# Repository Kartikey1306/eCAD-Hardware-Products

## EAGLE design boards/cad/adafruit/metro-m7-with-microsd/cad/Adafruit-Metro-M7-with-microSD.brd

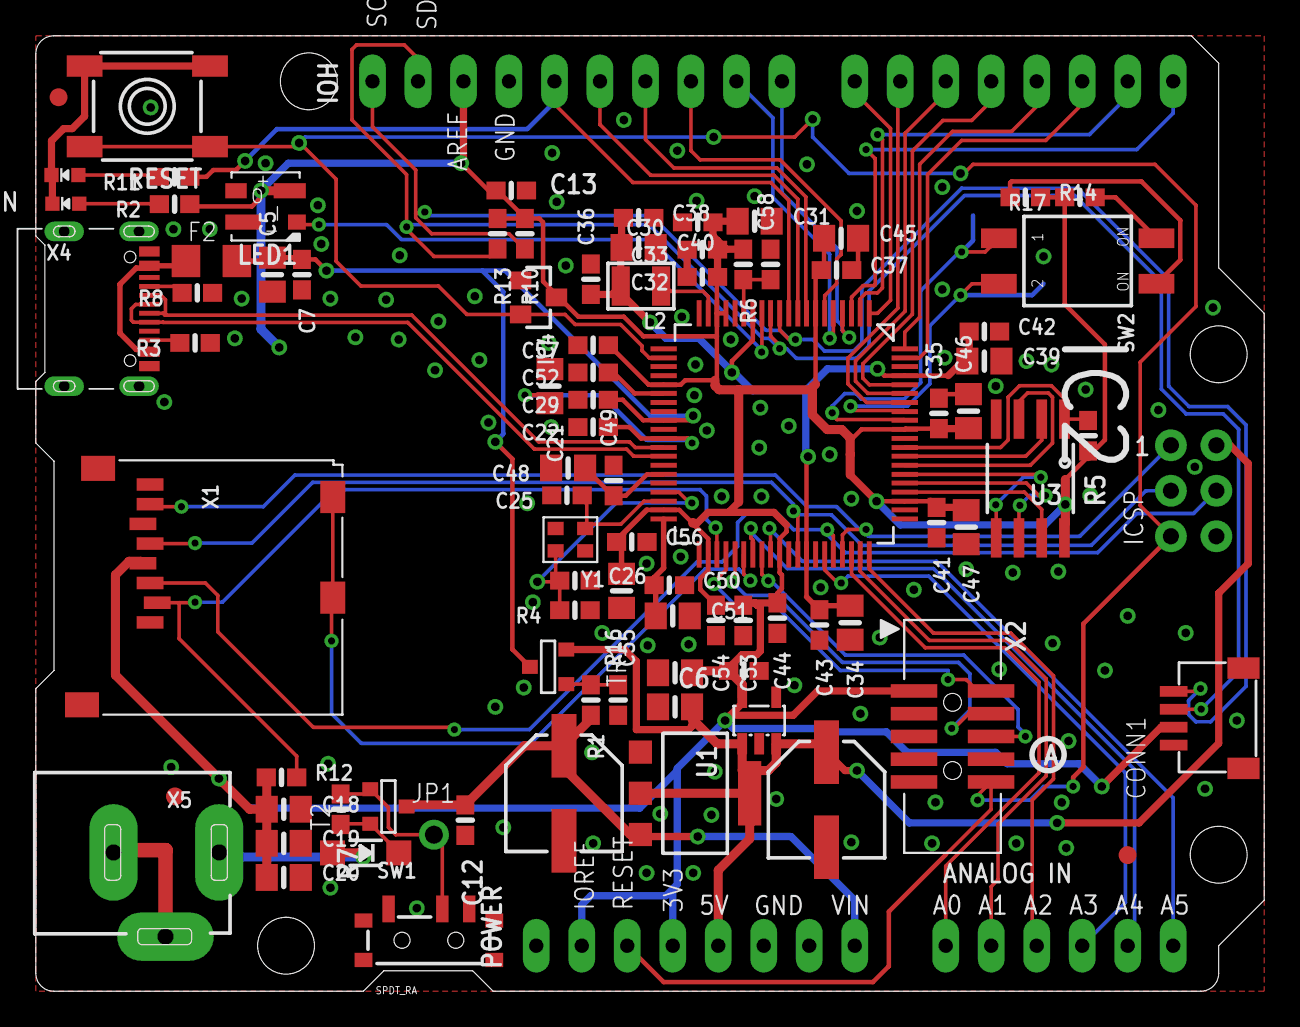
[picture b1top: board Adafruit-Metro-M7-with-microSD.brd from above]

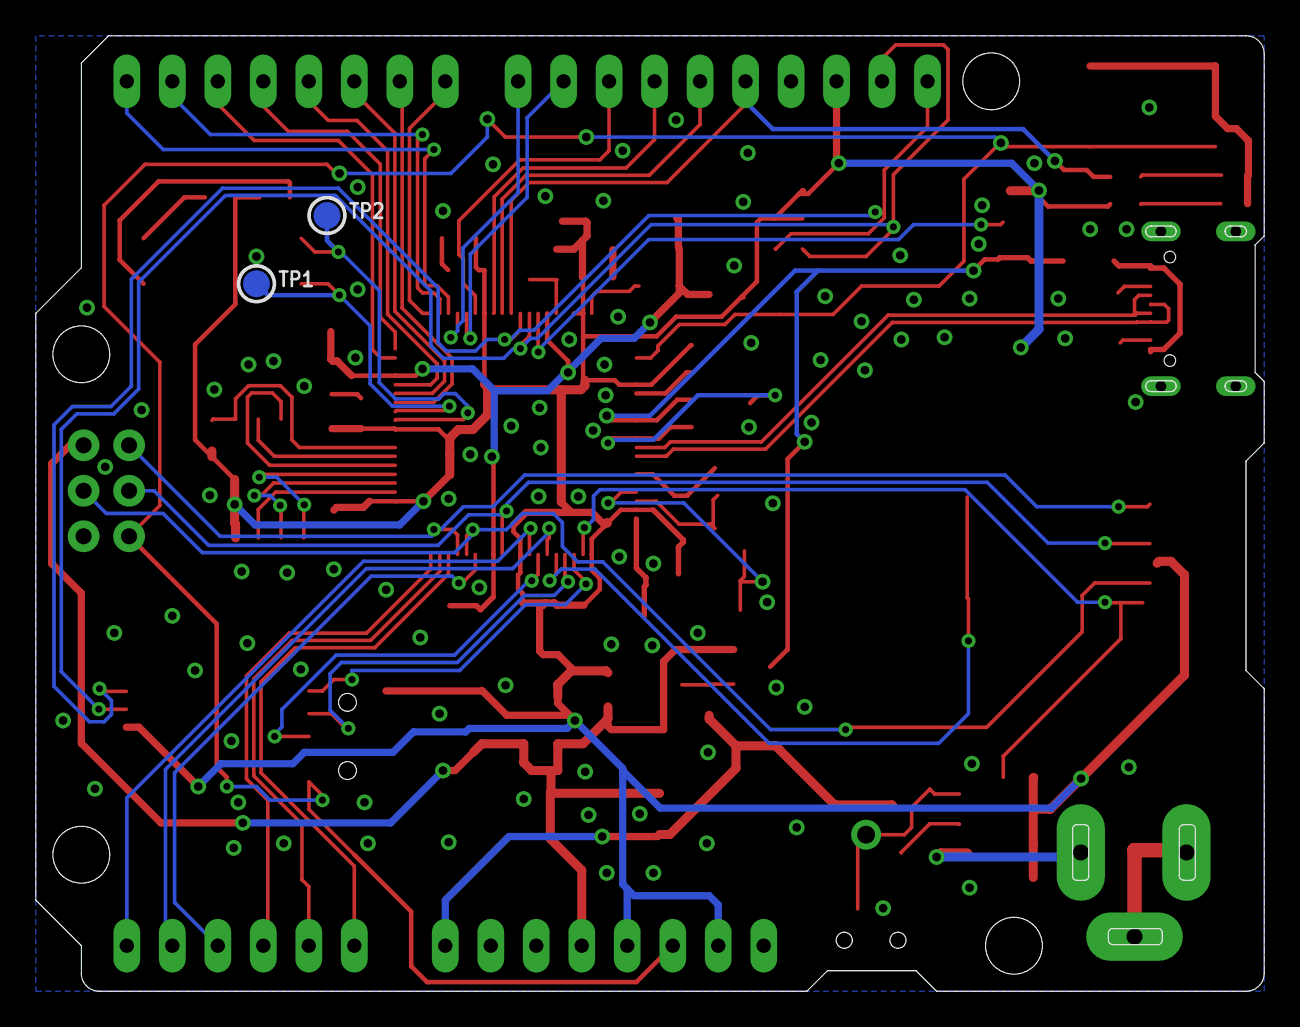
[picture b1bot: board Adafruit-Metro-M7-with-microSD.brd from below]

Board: 2 copper layers, 68.6 x 53.3 mm, 97 parts (3 on the bottom side), 67 nets.

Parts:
AD: 1x6F; 1X06_OVALWAVE
C2, C3, C5, C18, C19, C20, C21, C31, C39, C40, C45, C46, C47, C48, C51, C55: 10uF; 0805-NO
C6, C7, C12, C13, C22, C32, C35, C37, C41, C43: 0.1uF; 0603-NO
C25, C26: 16pF; 0603-NO
C29, C30, C36, C42, C44, C54: 1uF; 0603-NO
C33, C38, C49, C50, C52, C53, C56, C57, C58: 0.22uF; 0603-NO
C34: 22uF; 0805-NO
CONN1: STEMMA_I2C_QT; JST_SH4
D1: MBR120; SOD-123
F2: FUSE; R1206
FD1, FD2, FD3: FIDUCIAL_1MM
IC2: IMX_RT1010; QFP50P1400X1400X160-80N
IC4: APX80X_SA; SOT23-WIDE
ICSP: 2x3M; 2X03_ROUND_70MIL
IOH: 1x10F; 1X10_OVALWAVE
IOL: 1x8F; 1X08_OVALWAVE
JP1: 1X01_ROUND
L: RED; CHIPLED_0603_NOOUTLINE
L2: 4.7uH; INDUCTOR_1007
LED1: WS2812B_3535FULL; LED3535_FULLPADS
ON: GREEN; CHIPLED_0603_NOOUTLINE
PC1, PC2: 47uF/25V; PANASONIC_D
POWER: 1x8F; 1X08_OVALWAVE
R1, R16: 100K; 0603-NO
R2, R3, R8, R11, R14, R17: 5.1K; 0603-NO
R4: 2.2M; 0603-NO
R5, R7, R10, R12, R13: 10K; 0603-NO
R6: 30K; 0603-NO
RESET: 6x6mm; 6MMX6MM_TACTILE_SMT
SW1: SPDT_RA; SPDT_SMT_SSSS811101
SW2: DIP2; DIPSWITCH_2PIN
T2: DMP3098L-7; SOT-23
TP1, TP2: TESTPOINT_ROUND_1.5MM
TR1: DMP3098L-7; SOT-23
U1: NCP1117ST50T3G; SOT223-R
U2: AP2112K-3.3; SOT23-DBV
U3: W25Q64JV; SOIC8_208MIL
U$11: PCBFEAT-REV-040
U$12: M7_RT1011SD_TOP
U$19: M7_RT1011SD_BOT
X1: MICROSD
X2: 2x5 0.05" SWD; 2X05_1.27MM_BOX_POSTS
X4: USB C; USB_C_CUSB31-CFM2AX-01-X
X5: 2.1mm; DCJACK_2MM_PTH
Y1: 24MHz 10pF; CRYSTAL_2.5X2

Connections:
3.3V: C3.2, C6.2, C13.1, C18.1, C19.1, C20.1, C30.1, C31.1, C32.1, C33.1, C35.1, C37.1, C41.1, C44.1, C45.1, C46.1, C47.1, C53.1, C54.1, C55.1, C56.1, C57.1, CONN1.2, IC2.7, IC2.17, IC2.18, IC2.25, IC2.39, IC2.42, IC2.50, IC2.63, IC2.71, IC4.3, IOH.3, LED1.2, POWER.2, POWER.4, R2.1, R5.2, R6.1, R10.1, R12.1, R13.1, R14.2, R17.2, U2.5, U3.8, X1.4, X2.1
!RESET: IC2.22, IC4.2, ICSP.5, POWER.3, RESET.B, RESET.B', X2.10
+5V: C2.2, ICSP.2, PC2.+, POWER.5, TR1.2, U1.2, U1.4, U2.1, U2.3
A0: AD.1, IC2.58
A1: AD.2, IC2.59
A2: AD.3, IC2.60
A3: AD.4, IC2.55
A4: AD.5, IC2.47
A5: AD.6, IC2.49
BOOT_MODE0: IC2.72, SW2.1OFF, TP2.P$1
BOOT_MODE1: IC2.73, SW2.2OFF, TP1.P$1
D2: IC2.79, IOL.6
D3: IC2.80, IOL.5
D4: IC2.76, IOL.4
D5: IC2.75, IOL.3
D6: IC2.74, IOL.2
D7: IC2.1, IOL.1
D8: IC2.4, IOH.10
D9: IC2.5, IOH.9
D10: IC2.6, IOH.8
D11: IC2.8, IOH.7
D12: IC2.9, IOH.6
D13: IC2.10, IOH.5, R11.1
D+: IC2.33, X4.A6, X4.B6
D-: IC2.32, X4.A7, X4.B7
DCDC: IC2.19, L2.P$1
FLASH_CS: IC2.69, R5.1, U3.1
FLASH_IO0: IC2.66, U3.5
FLASH_IO1: IC2.68, U3.2
FLASH_IO2: IC2.67, U3.3
FLASH_IO3: IC2.64, U3.7
FLASH_SCK: IC2.65, U3.6
GND: C2.1, C3.1, C5.1, C6.1, C7.2, C12.2, C13.2, C18.2, C19.2, C20.2, C21.1, C22.2, C25.2, C26.2, C29.2, C30.2, C31.2, C32.2, C33.2, C34.2, C35.2, C36.2, C37.2, C38.2, C39.2, C40.2, C41.2, C42.2, C43.2, C44.2, C45.2, C46.2, C47.2, C48.2, C49.2, C50.2, C51.2, C52.2, C53.2, C54.2, C55.2, C56.2, C57.2, C58.2, CONN1.1, CONN1.MT1, CONN1.MT2, IC2.16, IC2.20, IC2.23, IC2.27, IC2.30, IC2.34, IC2.41, IC2.54, IC2.61, IC2.78, IC4.1, ICSP.6, IOH.4, L.C, LED1.4, ON.C, PC1.-, PC2.-, POWER.6, POWER.7, R3.1, R4.1, R8.1, R16.1, RESET.A, RESET.A', SW1.A, U1.1, U2.2, U3.4, X1.6, X1.MT1, X1.MT2, X2.3, X2.5, X4.A1B12, X4.B1A12, X5.GND, X5.GNDBREAK
MISO: IC2.57, ICSP.1, X1.7
MOSI: IC2.56, ICSP.4, X1.3
unnamed: L.A, R11.2
unnamed: ON.A, R2.2
unnamed: R14.1, SW2.2ON
unnamed: R17.1, SW2.1ON
unnamed: R8.2, X4.A5
unnamed: R3.2, X4.B5
unnamed: C26.1, IC2.37, R4.2, Y1.3
unnamed: C25.1, IC2.38, Y1.1
unnamed: R1.1, R16.2, TR1.3
unnamed: D1.C, R7.2, T2.2
NEOPIX: IC2.13, LED1.1
PSW: C58.1, IC2.15, R6.2
PWRIN: D1.A, X5.PWR
PWR_SWITCH: JP1.1, R7.1, SW1.B, T2.3
RXD: IC2.3, IOL.8
SCK: IC2.52, ICSP.3, X1.5
SCL: CONN1.4, IC2.11, IOH.1, R10.2
SDA: CONN1.3, IC2.12, IOH.2, R13.2
SD_CD: IC2.46, X1.CD1, X1.CD2
SD_CS: IC2.43, R12.2, X1.2
SVCS_CAP: C52.1, IC2.26
SWCLK: IC2.45, X2.4
SWDIO: IC2.44, X2.2
SWO: IC2.48, X2.6
TXD: IC2.2, IOL.7
USB_CAP: C21.2, C22.1, IC2.31
VBUS: C5.2, C7.1, C29.1, F2.2, IC2.29, TR1.1
VBUS_UNFUSE: F2.1, X4.A4B9, X4.B4A9
VDDA_1P1_CAP: C50.1, C51.1, IC2.40
VDDA_2P5_CAP: C48.1, C49.1, IC2.35
VDD_SOC_IN: C34.1, C36.1, C38.1, C39.1, C40.1, C42.1, C43.1, IC2.14, IC2.53, IC2.77, L2.P$2
VIN: C12.1, PC1.+, POWER.8, R1.2, T2.1, U1.3

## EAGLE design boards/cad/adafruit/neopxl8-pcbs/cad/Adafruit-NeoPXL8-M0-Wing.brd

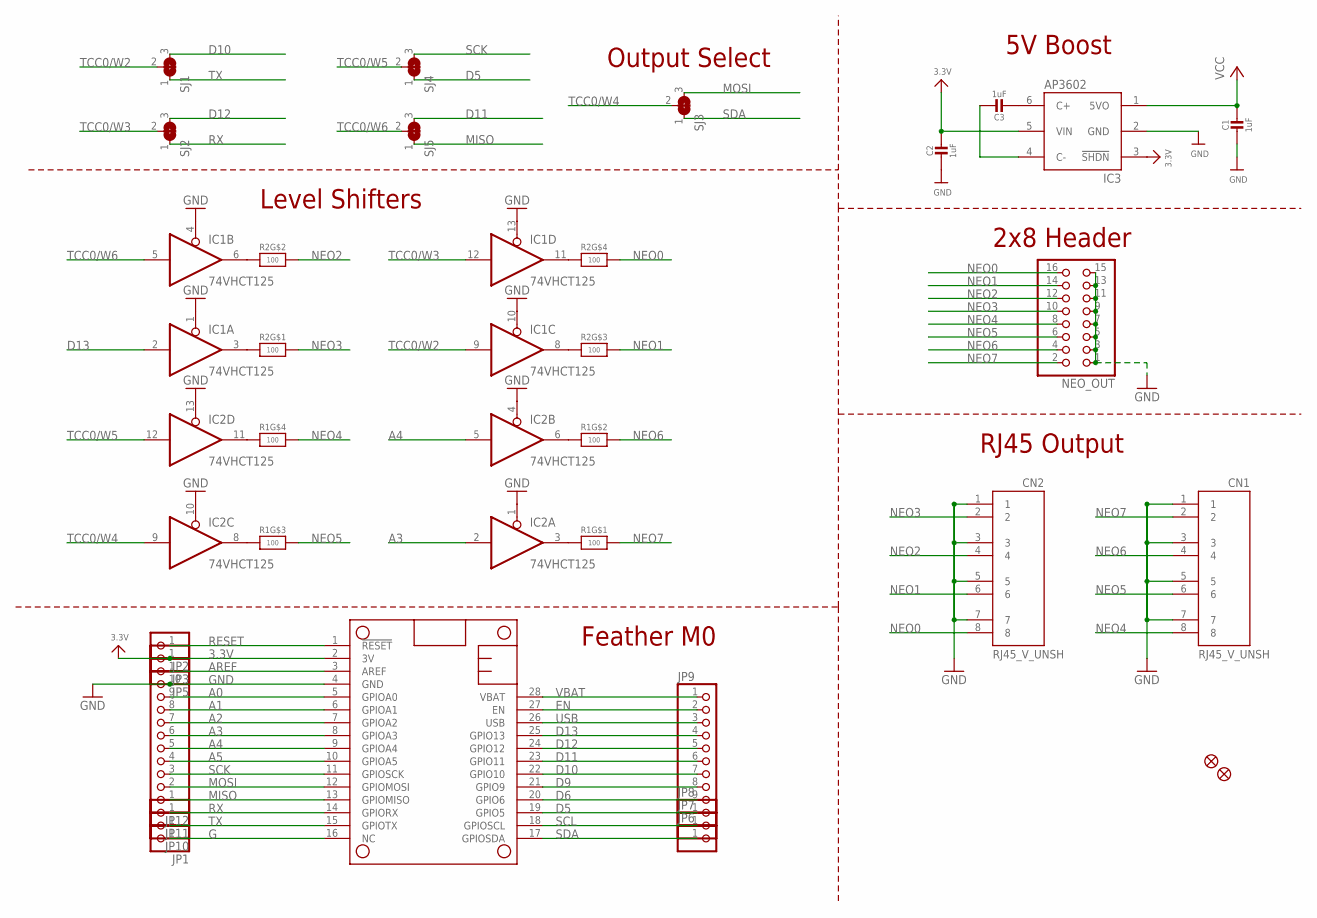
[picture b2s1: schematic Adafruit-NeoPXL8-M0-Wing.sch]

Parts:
C1, C2, C3: 1uF; 0603-NO
CN1, CN2: RJ45_V_UNSH; RJ45_VERTICAL_UNSHIELDED
FID1, FID2: FIDUCIAL_1MM
IC1, IC2: 74VHCT125; TSSOP14
IC3: AP3602; SOT23-6
JP1, JP2, JP3, JP5, JP6, JP7, JP8, JP10, JP11: HEADER-1X1ROUND; 1X01_ROUND
JP9: HEADER-1X970MIL; 1X09_ROUND_70
JP12: HEADER-1X10ROUND; 1X10_ROUND
MS1: FEATHERWING
NEO_OUT: HEADER-2X8; 2X08
R1, R2: 100; RESPACK_4X0603
SJ1, SJ2, SJ3, SJ4, SJ5: SOLDERJUMPER_2WAY; SOLDERJUMPER_2WAY_OPEN_NOPASTE

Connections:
3.3V: C2.1, IC3.3 (!SHDN), IC3.5 (VIN), JP3.1, MS1.2 (3V)
A0: JP12.9, MS1.5 (GPIOA0)
A1: JP12.8, MS1.6 (GPIOA1)
A2: JP12.7, MS1.7 (GPIOA2)
A3: IC2.2 (I), JP12.6, MS1.8 (GPIOA3)
A4: IC2.5 (I), JP12.5, MS1.9 (GPIOA4)
A5: JP12.4, MS1.10 (GPIOA5)
AREF: JP5.1, MS1.3 (AREF)
D5: JP8.1, MS1.19 (GPIO5), SJ4.1
D6: JP9.9, MS1.20 (GPIO6)
D9: JP9.8, MS1.21 (GPIO9)
D10: JP9.7, MS1.22 (GPIO10), SJ1.3
D11: JP9.6, MS1.23 (GPIO11), SJ5.3
D12: JP9.5, MS1.24 (GPIO12), SJ2.3
D13: IC1.2 (I), JP9.4, MS1.25 (GPIO13)
EN: JP9.2, MS1.27 (EN)
G: JP1.1, MS1.16 (NC)
GND: C1.2, C2.2, CN1.1, CN1.3, CN1.5, CN1.7, CN2.1, CN2.3, CN2.5, CN2.7, IC1.1 (OE), IC1.4 (OE), IC1.7 (GND), IC1.10 (OE), IC1.13 (OE), IC2.1 (OE), IC2.4 (OE), IC2.7 (GND), IC2.10 (OE), IC2.13 (OE), IC3.2 (GND), JP12.10, MS1.4 (GND), NEO_OUT.1, NEO_OUT.3, NEO_OUT.5, NEO_OUT.7, NEO_OUT.9, NEO_OUT.11, NEO_OUT.13, NEO_OUT.15
MISO: JP12.1, MS1.13 (GPIOMISO), SJ5.1
MOSI: JP12.2, MS1.12 (GPIOMOSI), SJ3.3
unnamed: IC2.3 (O), R1.1
unnamed: IC1.11 (O), R2.4 (1)
unnamed: IC1.8 (O), R2.3 (1)
unnamed: IC1.6 (O), R2.2 (1)
unnamed: IC1.3 (O), R2.1
unnamed: IC2.6 (O), R1.2 (1)
unnamed: IC2.8 (O), R1.3 (1)
unnamed: IC2.11 (O), R1.4 (1)
unnamed: C3.2, IC3.6 (C+)
unnamed: C3.1, IC3.4 (C-)
NEO0: CN2.8, NEO_OUT.16, R2.5 (2)
NEO1: CN2.6, NEO_OUT.14, R2.6 (2)
NEO2: CN2.4, NEO_OUT.12, R2.7 (2)
NEO3: CN2.2, NEO_OUT.10, R2.8 (2)
NEO4: CN1.8, NEO_OUT.8, R1.5 (2)
NEO5: CN1.6, NEO_OUT.6, R1.6 (2)
NEO6: CN1.4, NEO_OUT.4, R1.7 (2)
NEO7: CN1.2, NEO_OUT.2, R1.8 (2)
RESET: JP2.1, MS1.1 (!RESET)
RX: JP11.1, MS1.14 (GPIORX), SJ2.1
SCK: JP12.3, MS1.11 (GPIOSCK), SJ4.3
SCL: JP7.1, MS1.18 (GPIOSCL)
SDA: JP6.1, MS1.17 (GPIOSDA), SJ3.1
TCC0/W2: IC1.9 (I), SJ1.2
TCC0/W3: IC1.12 (I), SJ2.2
TCC0/W4: IC2.9 (I), SJ3.2
TCC0/W5: IC2.12 (I), SJ4.2
TCC0/W6: IC1.5 (I), SJ5.2
TX: JP10.1, MS1.15 (GPIOTX), SJ1.1
USB: JP9.3, MS1.26 (USB)
VBAT: JP9.1, MS1.28 (VBAT)
VCC: C1.1, IC1.14 (VCC), IC2.14 (VCC), IC3.1 (5VO)

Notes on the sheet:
5V Boost
Output Select
Level Shifters
Feather M0
2x8 Header
RJ45 Output

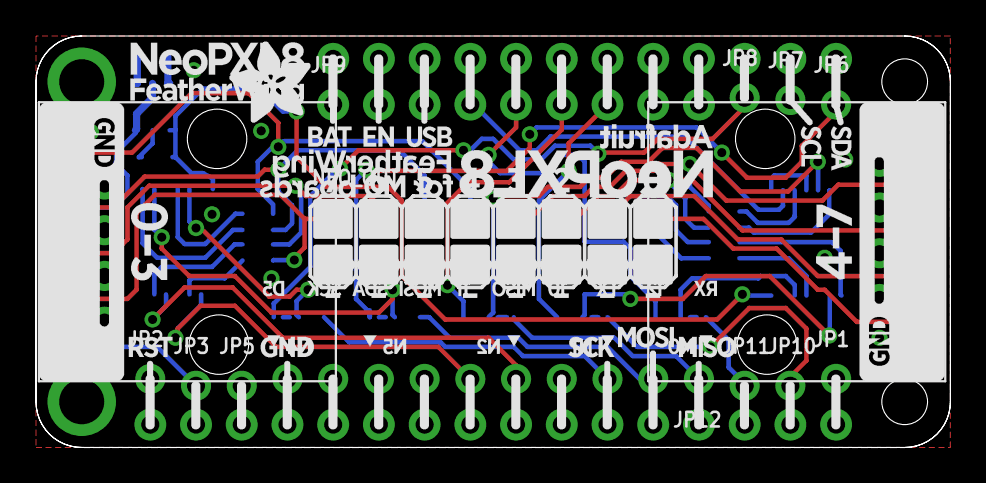
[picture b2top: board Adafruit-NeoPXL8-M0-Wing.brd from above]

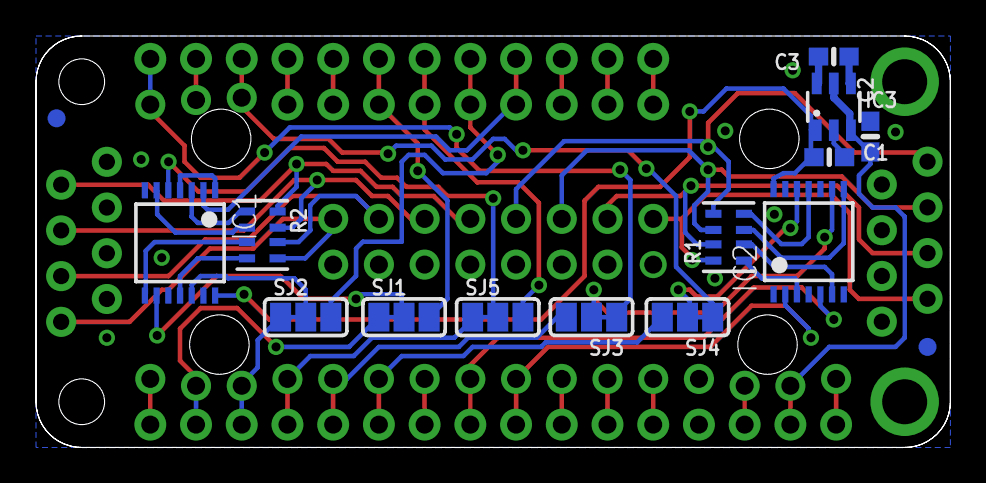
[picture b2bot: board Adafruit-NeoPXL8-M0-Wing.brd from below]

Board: 2 copper layers, 50.8 x 22.9 mm, 32 parts (16 on the bottom side), 52 nets.

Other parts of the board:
U$7: NEOPXL8_TOP
U$8: NEOPXL8_BOT

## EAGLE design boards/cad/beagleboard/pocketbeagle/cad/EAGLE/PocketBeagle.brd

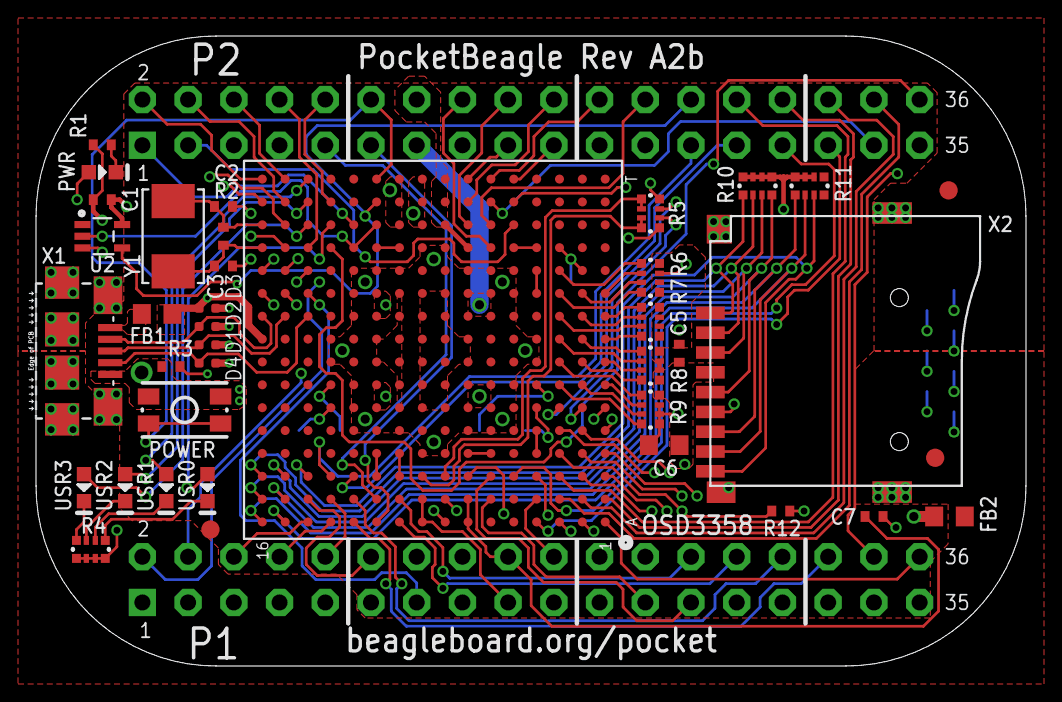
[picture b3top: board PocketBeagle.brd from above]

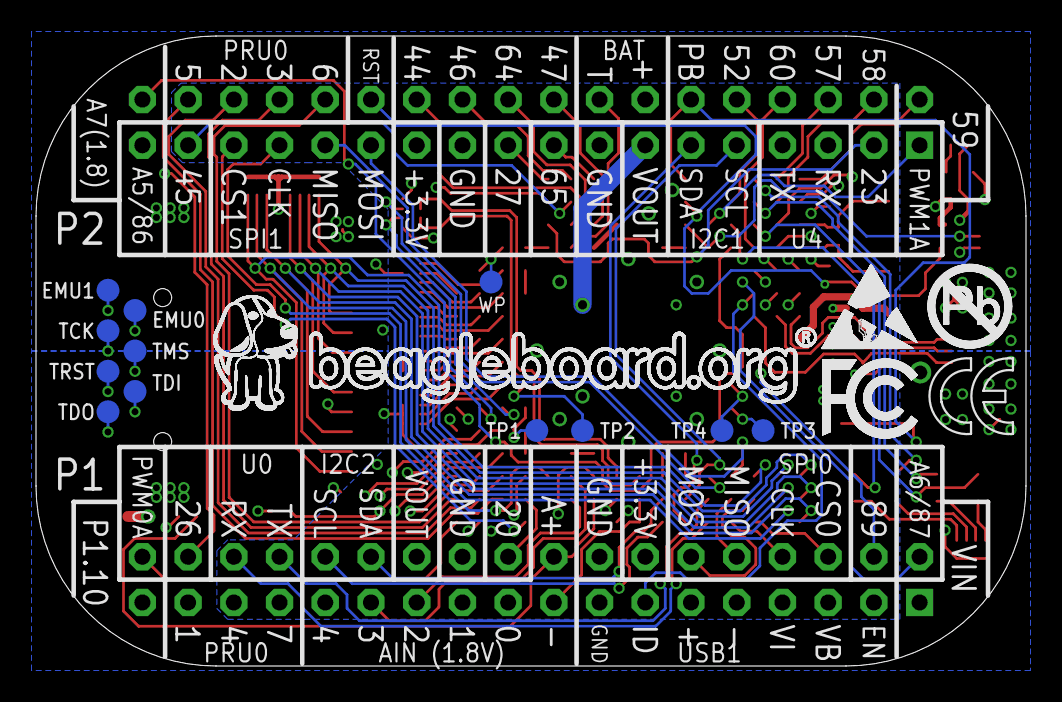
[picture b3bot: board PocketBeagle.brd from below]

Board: 4 copper layers, 55.0 x 35.0 mm, 57 parts (17 on the bottom side), 133 nets.

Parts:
C1, C5, C7: 0.1uF, 6.3V; 0402
C2, C3: 22pF, 50V; 0402
C6: 10uF, 10V; 0603
D1, D2, D3, D4: ESD-0402-NO-SILK
EMU0, EMU1: PTR1B1,27; B1,27
FB1, FB2: 0603
FUD1, FUD2, FUD3: FIDUCIAL; FIDUCIAL_40MIL
P1, P2: TH-2X18-(35MIL-DIA)-W/O-SILK
POWER: MINI_PUSHBUTTON
PWR: LTST-C191TBKT; 0603-LED
R1: 1k; 0402
R2: 1M, 1%; 0402
R3, R12: 10k; 0402
R4: 1k; RN0804
R5, R10, R11: 10k; RN0804
R6, R7, R8, R9: 100k; RN0804
TCK: PTR1B1,27; B1,27
TDI: PTR1B1,27; B1,27
TDO: PTR1B1,27; B1,27
TMS: PTR1B1,27; B1,27
TP1, TP2, TP3, TP4: PTR1B1,27; B1,27
TRST: PTR1B1,27; B1,27
U1: OSD3358-512M-BSM; OSD335X-BGA-256
U2: SN74LVC1G07DCK; SC70(TI-DCK)
U$1: CE_EMPTY_4_2MM
U$2: FCC_4_2MM
U$3: PB_4_7MM
U$4: ESD_4_7MM
U$5: BEAGLEBOARD_LOGO_33_5X6_5MM
USR0, USR1, USR2, USR3: LTST-C191TBKT; 0603-LED
WP: PTR1B1,27; B1,27
X1: 10118192-0001LF; 10118192-0001LF(MICRO-USB-B-AMPHENOL-FCI)
X2: MICROSD
Y1: 24 MHz 20pF; CRYSTAL_5X3.2MM

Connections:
3.3V: C5.1, C6.1, P1.14, P2.23, R6.7, R8.5, R9.4, R10.5, R10.6, R10.7, R10.8, R11.2, R11.3, R11.4, U1.F6, U1.F7, U1.G6, U1.G7, X2.4
(U1.A15)MMC0.D1: R11.6, U1.A15, X2.8
(U1.A16)MMC0.D0: R11.5, U1.A16, X2.7
(U1.B15)MMC0.CLK: R10.4, U1.B15, X2.5
(U1.B16)MMC0.CMD: R10.3, U1.B16, X2.3
(U1.C8)AIN5~1.8V: R5.1, R5.2, U1.C8
(U1.C9)AIN6~1.8V: R5.3, R5.4, U1.C9
(U1.C14)MMC0.CD: R11.7, U1.C14, X2.9
(U1.C15)MMC0.D3: R10.2, U1.C15, X2.2
(U1.C16)MMC0.D2: R10.1, U1.C16, X2.1
(U1.G1)LCD.D2.B5: R9.6, U1.G1
(U1.G2)LCD.D1.B4: R9.7, U1.G2
(U1.G3)LCD.D0.B3: R9.8, U1.G3
(U1.H1)LCD.D5.G2: R8.3, U1.H1
(U1.H2)LCD.D4.B7: R8.4, U1.H2
(U1.H3)LCD.D3.B6: R9.5, U1.H3
(U1.J1)LCD.D8.G5: R7.4, U1.J1
(U1.J2)LCD.D7.G4: R8.1, U1.J2
(U1.J3)LCD.D6.G3: R8.2, U1.J3
(U1.K1)LCD.D11.R3: R7.1, U1.K1
(U1.K2)LCD.D10.G7: R7.2, U1.K2
(U1.K3)LCD.D9.G6: R7.3, U1.K3
(U1.K14)USBC.ID: D4.2, U1.K14, X1.ID
(U1.K15)USBC.D+: D1.2, U1.K15, X1.D+
(U1.K16)USBC.D-: D2.2, U1.K16, X1.D-
(U1.L1)LCD.D14.R6: R6.2, U1.L1
(U1.L2)LCD.D13.R5: R6.3, U1.L2
(U1.L3)LCD.D12.R4: R6.4, U1.L3
(U1.M2)EEPROM.WP: U1.M2, U1.N3, WP.TP
(U1.M3)LCD.D15.R7: R6.1, U1.M3
(U1.P13)USR0: U1.P13, USR0.A
(U1.P14)USR3: U1.P14, USR3.A
(U1.R14)USR2: U1.R14, USR2.A
(U1.T14)USR1: U1.T14, USR1.A
AIN0(1.8V): P1.19, U1.A8
AIN1(1.8V): P1.21, U1.B8
AIN2(1.8V): P1.23, U1.B6
AIN3(1.8V): P1.25, U1.C6
AIN4(1.8V): P1.27, U1.C7
AIN5(3.3V): P2.35, R5.7, U1.F3
AIN6/GPIO87: P1.2, R5.6, U1.F2
AIN7(1.8V): P2.36, U1.N13
AIN.VREF+: C7.1, P1.18, U1.A7, U1.B7
AIN.VREF-: C7.2, P1.17, U1.A9, U1.B9
BAT.TEMP: P2.16, U1.N6
BAT.VIN: P2.14, U1.N7, U1.P8, U1.R8, U1.T8
CGND: FB2.1, X1.CGND1, X1.CGND2, X1.CGND3, X1.CGND4, X1.CGND5, X1.CGND6, X2.G1, X2.G2, X2.G3, X2.G4
GND: C1.2, C5.2, C6.2, D1.1, D2.1, D3.1, D4.1, FB2.2, P1.15, P1.16, P1.22, P2.15, P2.21, POWER.1, POWER.2, R1.1, R3.1, R4.5, R4.6, R4.7, R4.8, R5.5, R5.8, R6.5, R6.6, R6.8, R7.5, R7.6, R7.7, R7.8, R8.6, R8.7, R8.8, R9.1, R9.2, R9.3, R12.1, U1.D8, U1.D9, U1.E5, U1.E6, U1.E7, U1.E8, U1.E9, U1.E10, U1.E11, U1.E12, U1.F5, U1.F12, U1.G5, U1.G12, U1.H4, U1.H5, U1.H12, U1.H13, U1.J4, U1.J5, U1.J12, U1.J13, U1.K5, U1.K12, U1.L5, U1.L12, U1.M5, U1.M6, U1.M7, U1.M8, U1.M9, U1.M10, U1.M11, U1.M12, U1.N8, U1.N9, U2.3, X1.GND, X2.6
GPIO20: P1.20, U1.B4
GPIO23: P2.3, U1.P5
GPIO26: P1.34, U1.R5
GPIO27: P2.19, U1.T5
GPIO44: P2.24, U1.P6
GPIO45: P2.33, U1.R6
GPIO46: P2.22, U1.T6
GPIO47: P2.18, U1.P7
GPIO52: P2.10, U1.R13
GPIO57: P2.6, U1.T15
GPIO58: P2.4, U1.R15
GPIO59: P2.2, U1.T16
GPIO60: P2.8, U1.N14
GPIO64: P2.20, U1.R7
GPIO65: P2.17, U1.T7
GPIO89: P1.4, U1.E1
I2C1.SCL: P2.9, U1.B11
I2C1.SDA: P2.11, U1.A11
I2C2.SCL: P1.28, U1.A10
I2C2.SDA: P1.26, U1.B10
JTAG_EMU0: EMU0.TP, U1.E2
JTAG_EMU1: EMU1.TP, U1.E3
JTAG_TCK: TCK.TP, U1.D1
JTAG_TDI: TDI.TP, U1.C1
JTAG_TDO: TDO.TP, U1.C2
JTAG_TMS: TMS.TP, U1.D2
JTAG_TRST#: R12.2, TRST.TP, U1.D3
unnamed: R4.3, USR2.K
unnamed: R4.4, USR3.K
unnamed: PWR.K, R1.2
unnamed: R4.2, USR1.K
unnamed: R4.1, USR0.K
unnamed: TP1.TP, U1.F4
unnamed: TP2.TP, U1.G4
unnamed: TP3.TP, U1.F13
unnamed: TP4.TP, U1.G13
unnamed: U1.D6, U1.D7
unnamed: R3.2, U1.M16
unnamed: U1.N4, U1.N5
unnamed: U1.L4, U1.M4
unnamed: U1.D4, U1.E4
unnamed: U1.N10, U1.N11
unnamed: U1.C11, U1.D11
unnamed: U1.C10, U1.D10
OSC.GND: C2.1, C3.1, U1.N15
OSC.IN: C2.2, R2.2, U1.P16, Y1.2
OSC.OUT: C3.2, R2.1, U1.N16, Y1.1
PMIC_PGOOD: U1.N12, U1.P11, U2.2
PRU0.1: P1.33, U1.A2
PRU0.2: P2.32, U1.B2
PRU0.3: P2.30, U1.B1
PRU0.4: P1.31, U1.A3
PRU0.5: P2.34, U1.B3
PRU0.6: P2.28, U1.C3
PRU0.7: P1.29, U1.C4
PRU1.10: P1.35, U1.F1
PWM0A: P1.36, U1.A1
PWM1A: P2.1, U1.P12
PWR.BTN: P2.12, POWER.3, POWER.4, U1.T11
RESET#: P2.26, U1.R11, U2.4
SPI0.CLK: P1.8, U1.A13
SPI0.CS: P1.6, U1.A14
SPI0.MISO: P1.10, U1.B13
SPI0.MOSI: P1.12, U1.B14
SPI1.CLK: P2.29, U1.C5
SPI1.CS: P2.31, U1.A4
SPI1.MISO: P2.27, U1.C12
SPI1.MOSI: P2.25, U1.C13
UART0.RX: P1.32, U1.A12
UART0.TX: P1.30, U1.B12
UART4.RX: P2.5, U1.P15
UART4.TX: P2.7, U1.R16
USB1.D+: P1.11, U1.L15
USB1.D-: P1.9, U1.L16
USB1.DRVVBUS: P1.3, U1.M14
USB1.ID: P1.13, U1.L14
USB1.VBUS: P1.5, U1.M15
VBUS.RAW: FB1.1, X1.VBUS
VDD_1V8: U1.F10, U1.G10, U1.H10, U1.H11, U1.J10, U1.J11, U1.K10, U1.L10
VDD_3V3A: U1.F8, U1.F9, U1.G8, U1.G9, U1.H7, U1.H8, U1.H9, U1.J7, U1.J8, U1.J9, U1.K8, U1.K9, U1.L8, U1.L9
VDD_3V3AUX: PWR.A, U1.F11, U1.G11
VDD_RTC: C1.1, U1.K11, U1.L11, U2.5
VIN: P1.1, U1.P10, U1.R10, U1.T10
VIN.USB: D3.2, FB1.2, P1.7, U1.J16, U1.P9, U1.R9, U1.T9
VOUT: P1.24, P2.13, U1.K6, U1.K7, U1.L6, U1.L7

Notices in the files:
parts and their libraries:
microbuilder: This work is placed in the public domain, and may be freely used for commercial and non-commercial work with the following conditions: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
SparkFun-Aesthetics: Licensing: Creative Commons ShareAlike 4.0 International - https://creativecommons.org/licenses/by-sa/4.0
